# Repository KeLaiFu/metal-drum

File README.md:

This is a clone of a well known drum module, it has been tested, and with a few fixes, works fine.
The main issue is the transistors are 'flipped', this is due to the pin numbering being different between the THT and SMD versions within kicad. You can fix this by turning the transistor over and fitting it upside down. Theres one j111X component which doesnt have this problem and should be fitted as normal.

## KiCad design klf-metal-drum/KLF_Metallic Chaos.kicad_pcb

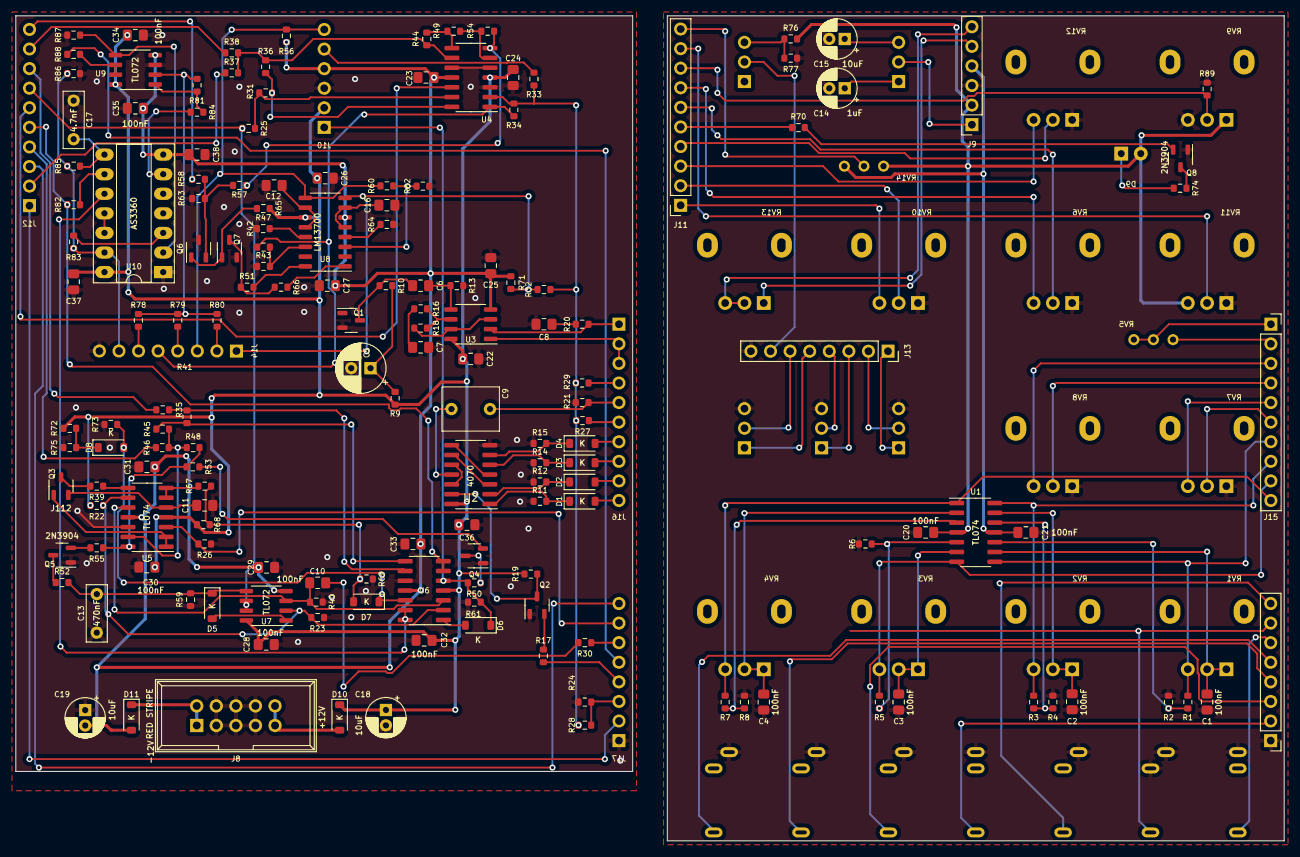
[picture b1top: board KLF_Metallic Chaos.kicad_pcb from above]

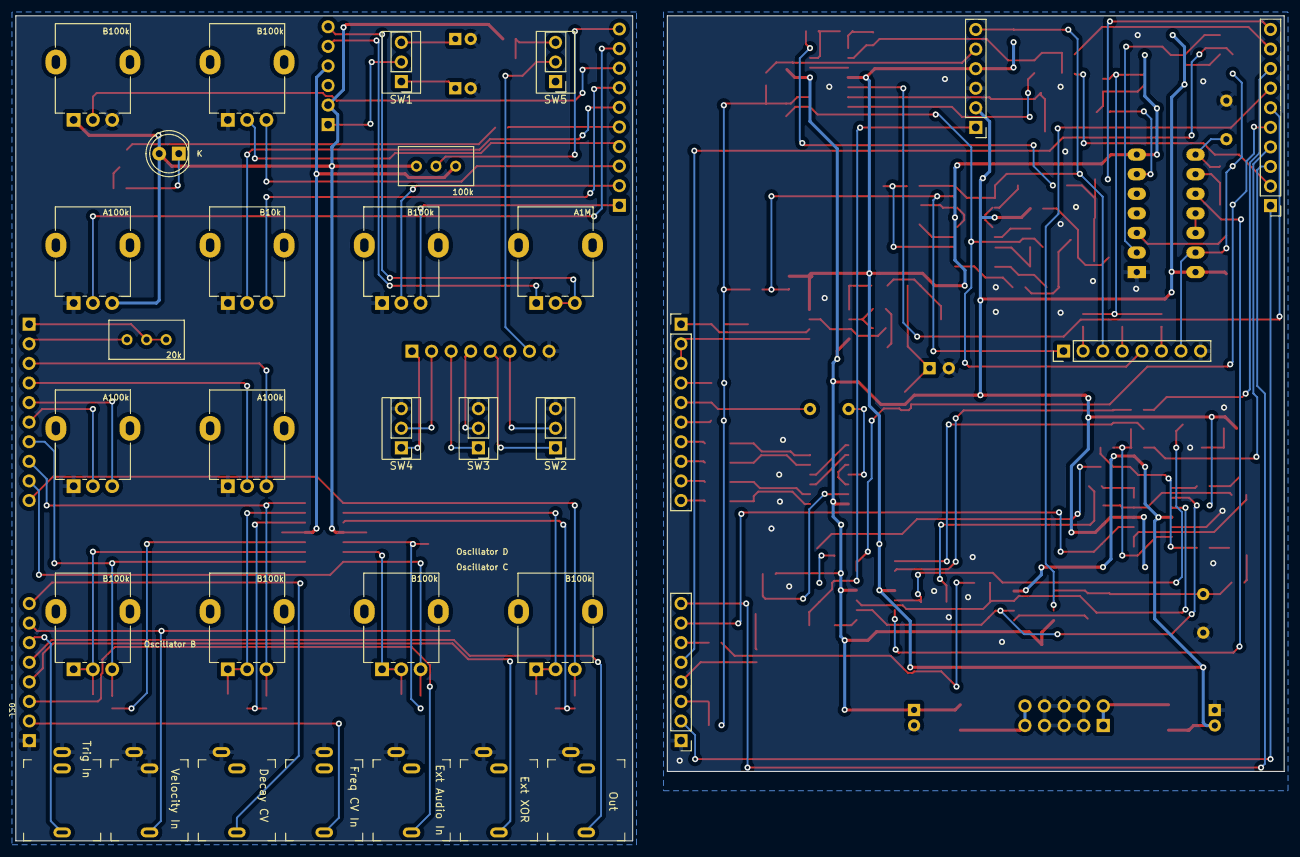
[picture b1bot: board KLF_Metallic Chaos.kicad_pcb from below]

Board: 2 copper layers, 164.5 x 107.0 mm, 193 parts (32 on the bottom side), 149 nets.

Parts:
C1, C2, C3, C4, C11, C20, C21, C22, C23, C24, C25, C26, C27, C28, C29, C30, C31, C32, C33, C34, C35, C36, C37, C38: 100nF; C_0805_2012Metric_Pad1.18x1.45mm_HandSolder
C5: 47uF; CP_Radial_D6.3mm_P2.50mm
C6, C10: 10nF; C_0805_2012Metric_Pad1.18x1.45mm_HandSolder
C7, C8: 220nF; C_0805_2012Metric_Pad1.18x1.45mm_HandSolder
C9: 1uF; C_Rect_L7.2mm_W5.5mm_P5.00mm_FKS2_FKP2_MKS2_MKP2
C12, C16: 150pF; C_0805_2012Metric_Pad1.18x1.45mm_HandSolder
C13: 470nF; C_Rect_L7.2mm_W2.5mm_P5.00mm_FKS2_FKP2_MKS2_MKP2
C14: 1uF; CP_Radial_D5.0mm_P2.00mm
C15, C18, C19: 10uF; CP_Radial_D5.0mm_P2.00mm
C17: 4.7nF; C_Rect_L7.2mm_W2.5mm_P5.00mm_FKS2_FKP2_MKS2_MKP2
D1, D2, D3, D4, D5, D6, D7, D8: 1N4148; D_SOD-123
D9: LED; LED_D5.0mm
D10, D11: 1N5817; D_SOD-123
J1: Ext XOR; PJ-301-M-12
J2: Freq CV In; PJ-301-M-12
J3: Ext Audio In; PJ-301-M-12
J4: Velocity In; PJ-301-M-12
J5: Trig In; PJ-301-M-12
J6: Decay CV; PJ-301-M-12
J7: Out; PJ-301-M-12
J8: Power_2x5; Power_Header
J9: Conn_01x06_Female; PinSocket_1x06_P2.54mm_Vertical
J10: Conn_01x06_Male; PinHeader_1x06_P2.54mm_Vertical
J11, J15: Conn_01x10_Female; PinSocket_1x10_P2.54mm_Vertical
J12, J16: Conn_01x10_Male; PinHeader_1x10_P2.54mm_Vertical
J13: Conn_01x08_Female; PinSocket_1x08_P2.54mm_Vertical
J14, J17, J20: Conn_01x08_Male; PinHeader_1x08_P2.54mm_Vertical
Q1: BC550; SOT-23-3
Q2, Q4, Q5, Q8: 2N3904; SOT-23-3
Q3: J112; SOT-23-3
Q6, Q7: 2N3906; SOT-23-3
R1, R3, R5, R7, R10, R11, R12, R13, R14, R15, R17, R18, R22, R24, R26, R27, R28, R29, R30, R32, R33, R34, R35, R37, R38, R40, R41, R44, R49, R54, R69, R73, R78, R79, R80, R81: 100k; R_0603_1608Metric
R2, R4, R6, R8, R45, R46, R48, R50, R51, R58, R65, R66, R70: 10k; R_0603_1608Metric
R9, R85, R89: 4.7k; R_0603_1608Metric
R16, R20, R23, R43, R47, R52, R62, R63, R64, R74, R88: 1k; R_0603_1608Metric
R19, R39, R53, R55, R59, R61: 1M; R_0603_1608Metric
R21: 1.5k; R_0603_1608Metric
R25, R31, R77: 20k; R_0603_1608Metric
R36, R68: 470k; R_0603_1608Metric
R42, R60: 200k; R_0603_1608Metric
R56, R71: 68k; R_0603_1608Metric
R57, R76, R82, R84, R87: 47k; R_0603_1608Metric
R67: 300k; R_0603_1608Metric
R72: 220k; R_0603_1608Metric
R75, R86: 30k; R_0603_1608Metric
R83: 15k; R_0603_1608Metric
RV1, RV2, RV3, RV4, RV9, RV10, RV12: B100k; Potentiometer_Alpha_RD901F-40-00D_Single_Vertical_centered
RV5: 20k; Potentiometer_Bourns_3296W_Vertical_screw_centered
RV6: B10k; Potentiometer_Alpha_RD901F-40-00D_Single_Vertical_centered
RV7, RV8, RV11: A100k; Potentiometer_Alpha_RD901F-40-00D_Single_Vertical_centered
RV13: A1M; Potentiometer_Alpha_RD901F-40-00D_Single_Vertical_centered
RV14: 100k; Potentiometer_Bourns_3296W_Vertical_screw_centered
SW1: Decay Short/Long; blue switch
SW2: HP; blue switch
SW3: BP; blue switch
SW4: LP; blue switch
SW5: VCA On/Off; blue switch
U1, U4, U5, U6: TL074; SO-14_3.9x8.65mm_P1.27mm
U2: 4070; SO-14_3.9x8.65mm_P1.27mm
U3, U7, U9: TL072; SO-8_3.9x4.9mm_P1.27mm
U8: LM13700; SO-16_3.9x9.9mm_P1.27mm
U10: AS3360; DIP-14_W7.62mm_Socket_LongPads

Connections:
+12V: C18.1, C20.2, C22.2, C24.2, C26.2, C28.2, C30.2, C32.2, C34.2, C36.2, C37.2, D9.2 (A), D10.1 (K), J9.2, J10.2, R9.2, R19.2, R22.2, R65.2, R68.2, R72.1, R76.2, RV9.1, RV11.3, RV14.1, U1.4 (V+), U2.14 (VDD), U3.8 (V+), U4.4 (V+), U5.4 (V+), U6.4 (V+), U7.8 (V+), U8.11 (V+), U9.8 (V+), U10.14 (VCC)
-12V: C19.2, C21.1, C23.1, C25.1, C27.1, C29.1, C31.1, C33.1, C35.1, C38.1, D11.2 (A), J9.4, J10.4, R56.1, R71.1, RV14.3, U1.11 (V-), U3.4 (V-), U4.11 (V-), U5.11 (V-), U6.11 (V-), U7.4 (V-), U8.6 (V-), U9.4 (V-), U10.7 (VEE)
BP2_A: J13.4, SW3.2 (B)
BP2_B: J14.4, R79.1
BP_A: J13.3, SW3.1 (A)
BP_B: J10.6, J14.3, R56.2, R60.1, U8.9
CVTrim_A: J11.10, RV14.2
CVTrim_B: J12.10, R58.1
Dec2_A: J11.8, R89.2, RV9.2
Dec2_B: J12.8, R35.1
DecCV_In_A: J11.3, RV12.3
DecCV_In_B: J6.T, J12.3, J17.decay_cv (Pin_8), J20.decay_cv (Pin_8)
Dec_A: J11.4, RV12.2
Dec_B: J12.4, R46.1
FilterCV: J12.7, R25.1, U7.6 (-), U7.7
FreqCV_A: J11.2, RV10.2
FreqCV_B: J12.2, R37.1
FreqCV_In_A: J11.1, RV10.3
FreqCV_In_B: J2.T, J12.1, J17.2, J20.2
FreqM1_A: J11.7, RV6.3
FreqM2_A: J11.6, RV6.2
FreqM2_B: J12.6, U4.12 (+)
Freq_A: J11.9, RV11.2
Freq_B: J12.9, R38.1
GND: C1.2, C2.2, C3.2, C4.2, C5.2, C7.2, C8.2, C11.2, C12.2, C13.1, C14.2, C15.2, C16.2, C17.1, C18.2, C19.1, C20.1, C21.2, C22.1, C23.2, C24.1, C25.2, C26.1, C27.2, C28.1, C29.2, C30.1, C31.2, C32.1, C33.2, C34.1, C35.2, C36.1, C37.1, C38.2, J1.S, J2.S, J3.S, J4.S, J4.TN, J5.S, J6.S, J7.S, J8.3, J8.4, J8.5, J8.6, J8.7, J8.8, J9.3, J10.3, J13.8, J14.8, J17.1, J20.1, Q1.2 (B), Q2.1 (E), Q4.1 (E), Q5.1 (E), Q6.3 (C), Q7.2 (B), Q8.1 (E), R2.1, R4.1, R6.1, R8.1, R11.1, R12.1, R13.1, R14.1, R15.1, R21.1, R23.1, R24.1, R26.1, R40.1, R43.1, R47.1, R59.1, R61.1, R62.1, R63.1, R64.1, R69.1, R73.1, R75.2, R77.1, R86.1, R87.1, R89.1, RV6.1, RV7.1, RV8.1, RV9.3, RV10.1, RV11.1, RV12.1, SW2.3 (C), SW3.3 (C), SW4.3 (C), U2.7 (VSS), U4.3 (+), U4.5 (+), U4.10 (+), U5.12 (+), U6.10 (+), U9.3 (+), U10.1 (GND)
HP2_A: J13.6, SW2.2 (B)
HP2_B: J14.6, R78.1
HP_A: J13.5, SW2.1 (A)
HP_B: J14.5, R34.2, R42.1, U4.1
LED_A: J11.5, R70.1
LED_B: J12.5, R82.1, U6.6 (-), U6.7
LP2_A: J13.2, SW4.2 (B)
LP2_B: J14.2, R80.1
LP_A: J13.1, SW4.1 (A)
LP_B: J14.1, R32.2, R71.2, U8.8
unnamed: C5.1, R9.1, R10.2
unnamed: C7.1, R16.1
unnamed: C8.1, R20.1
unnamed: C9.1, U2.11
unnamed: C10.1, R30.2
unnamed: C12.1, U8.10, U8.12
unnamed: C16.1, U8.5, U8.7
unnamed: D1.1 (K), R11.2, U2.1
unnamed: D2.1 (K), R12.2, U2.2
unnamed: D3.1 (K), R14.2, U2.5
unnamed: D4.1 (K), R15.2, U2.6
unnamed: D5.2 (A), U7.1
unnamed: C13.2, D5.1 (K), R52.2, R59.2, U7.5 (+)
unnamed: D6.2 (A), U6.1
unnamed: D7.2 (A), R67.2, R68.1, R69.2
unnamed: D7.1 (K), D8.2 (A), R73.2, U6.12 (+)
unnamed: D8.1 (K), R72.2, R75.1
unnamed: D9.1 (K), R74.2
unnamed: D10.2 (A), J8.9, J8.10
unnamed: D11.1 (K), J8.1, J8.2
unnamed: J1.T, J17.4, J20.4, R17.1
unnamed: J3.T, J17.3, J20.3, R24.2, R28.1
unnamed: J5.T, J17.6, J20.6, R30.1
unnamed: J7.T, J17.5, J20.5, R88.2
unnamed: C6.1, Q1.3 (E), R10.1
unnamed: Q2.2 (B), R17.2
unnamed: Q2.3 (C), R19.1, U2.13
unnamed: Q3.1 (D), U5.1, U5.2 (-)
unnamed: Q3.3 (G), R39.2
unnamed: C11.1, Q3.2 (S), U5.5 (+)
unnamed: Q4.2 (B), R53.2
unnamed: Q4.3 (C), R50.1
unnamed: Q5.2 (B), R55.2
unnamed: Q5.3 (C), R52.1
unnamed: Q6.2 (B), R57.2, R58.2, R63.2
unnamed: Q6.1 (E), Q7.1 (E), R65.1
unnamed: Q7.3 (C), R51.1, R66.1
unnamed: Q8.2 (B), R70.2
unnamed: Q8.3 (C), R74.1
unnamed: R31.2, R36.1, U4.14
unnamed: R39.1, U5.8
unnamed: R41.2, R45.1, U6.8
unnamed: R44.2, R49.1, U4.8
unnamed: R48.2, R53.1, R55.1, U5.14
unnamed: R51.2, U8.16
unnamed: R54.2, R57.1, U4.7
unnamed: R66.2, U8.1
unnamed: R81.2, R84.1, U9.1
unnamed: C14.1, SW1.1 (A)
unnamed: C15.1, SW1.3 (C)
unnamed: R76.1, R77.2, SW5.3 (C)
unnamed: R7.1, R8.2, U1.3 (+)
unnamed: C4.1, RV4.1, RV4.2, U1.2 (-)
unnamed: R5.1, R6.2, U1.5 (+)
unnamed: C3.1, RV3.1, RV3.2, U1.6 (-)
unnamed: R1.1, R2.2, U1.10 (+)
unnamed: C1.1, RV1.1, RV1.2, U1.9 (-)
unnamed: R3.1, R4.2, U1.12 (+)
unnamed: C2.1, RV2.1, RV2.2, U1.13 (-)
unnamed: U2.3, U2.9
unnamed: U2.4, U2.8
unnamed: U2.10, U2.12
unnamed: R18.1, U3.3 (+), U3.7
unnamed: C6.2, R13.2, U3.5 (+)
unnamed: R16.2, R18.2, U3.6 (-)
unnamed: R27.2, R28.2, R29.2, R32.1, R33.1, R34.1, U4.2 (-)
unnamed: R49.2, R54.1, U4.6 (-)
unnamed: R36.2, R37.2, R38.2, R44.1, U4.9 (-)
unnamed: R25.2, R31.1, U4.13 (-)
unnamed: J4.T, J17.7, J20.7, R26.2, U5.3 (+)
unnamed: R67.1, U5.6 (-), U5.7
unnamed: C10.2, R40.2, U5.10 (+), U6.3 (+), U7.3 (+)
unnamed: R45.2, R46.2, R48.1, U5.13 (-)
unnamed: R35.2, R41.1, U6.9 (-)
unnamed: R42.2, R43.2, U8.14 (+)
unnamed: R47.2, U8.13 (-)
unnamed: R60.2, R62.2, U8.3 (+)
unnamed: R64.2, U8.4 (-)
unnamed: R78.2, R79.2, R80.2, R81.1, U9.2 (-)
unnamed: R88.1, U9.6 (-), U9.7
unnamed: R84.2, U10.6 (II1)
unnamed: R87.2, U9.5 (+), U10.2 (IO1)
unnamed: R83.2, U10.3 (VE1)
unnamed: C17.2, R85.2, U10.8 (VREF)
unnamed: R82.2, U10.9 (II2)
unnamed: U6.13 (-), U6.14, U10.10 (VC2)
unnamed: U10.11 (VO2), U10.12 (VE2)
NoiseLvl1_A: J15.1, RV5.1, RV5.2
NoiseLvl1_B: J16.1, R20.2, U3.2 (-)
NoiseLvl2_A: J15.2, RV5.3
NoiseLvl2_B: J16.2, J16.3, U3.1
Noise_A: J15.3, RV8.3
Noise_Lvl_A: J15.4, RV8.2
Noise_Lvl_B: J16.4, R29.1
OSC1_A: J15.7, R1.2, RV1.3, U1.8
OSC1_B: D4.2 (A), J16.7
OSC2_A: J15.8, R3.2, RV2.3, U1.14
OSC2_B: D3.2 (A), J16.8
OSC3_A: J15.9, R5.2, RV3.3, U1.7
OSC3_B: D2.2 (A), J16.9
OSC4_A: J15.10, R7.2, RV4.3, U1.1
OSC4_B: D1.2 (A), J16.10
OSC_A: J15.5, RV7.3
OSC_B: C9.2, J16.5, R21.2
OSC_Lvl_A: J15.6, RV7.2
OSC_Lvl_B: J16.6, R27.1
Res1_A: J9.5, RV13.1
Res1_B: J10.5, R33.2
Res2_A: J9.6, RV13.2, RV13.3
Time_A: J9.1, SW1.2 (B)
Time_B: D6.1 (K), J10.1, R50.2, R61.2, U6.5 (+)
VCA_A: J13.7, SW5.2 (B)
VCA_B: J14.7, R83.1, R85.1, R86.2, U10.13 (IO2)
Vref: R22.1, R23.2, U5.9 (-), U6.2 (-), U7.2 (-)

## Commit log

2025-10-26 Add README content for drum module clone
    Added description about the drum module and transistor issues.

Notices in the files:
klf-metal-drum/KLF_Metallic Chaos.kicad_pcb:
CC0 1.0
